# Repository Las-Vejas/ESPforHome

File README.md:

# ESPforHome

A super small ESP32C6 devboard perfect for ESPHome.

It uses the ESP32-C6-MINI-1 and ESPHome for the software. 14 GPIO pins along with 2 GND, 1 3V3 and 1 5V pins are available to the user. The board is exactly 30mm x 30mm.

## BOM

The bom is available in /BOM.csv

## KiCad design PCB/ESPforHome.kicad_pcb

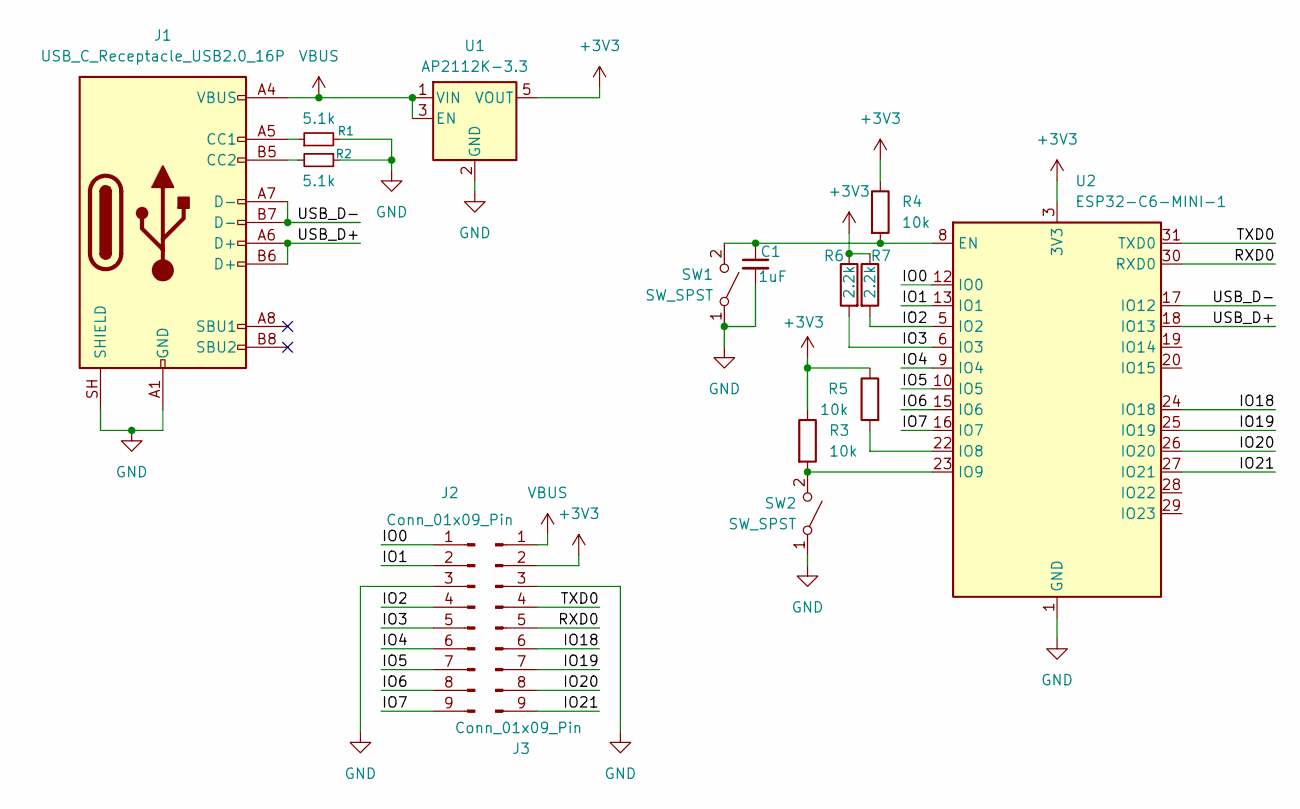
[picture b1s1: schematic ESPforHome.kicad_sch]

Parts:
C1: 1uF; C_0402_1005Metric; LCSC Part # C77009
J1: USB_C_Receptacle_USB2.0_16P; USB_C_Receptacle_GCT_USB4105-xx-A_16P_TopMnt_Horizontal; LCSC Part # C2765186
J2, J3: Conn_01x09_Pin; PinHeader_1x09_P2.54mm_Vertical; LCSC Part # C2883695
R1, R2: 5.1k; R_0402_1005Metric; LCSC Part # C2906874
R3, R4, R5: 10k; R_0402_1005Metric; LCSC Part # C2906861
R6, R7: 2.2k; R_0402_1005Metric; LCSC Part # C2906865
SW1, SW2: SW_SPST; SW_Push_SPST_NO_Alps_SKRK; LCSC Part # C49234124
U1: AP2112K-3.3; SOT-23-5; LCSC Part # C22365427
U2: ESP32-C6-MINI-1; LCSC Part # C5736265

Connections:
+3V3: J3.2, R3.1, R4.1, R5.1, R6.1, R7.1, U1.5 (VOUT), U2.3 (3V3)
/IO0: J2.1, U2.12 (IO0)
/IO1: J2.2, U2.13 (IO1)
/IO2: J2.4, R7.2, U2.5 (IO2)
/IO3: J2.5, R6.2, U2.6 (IO3)
/IO4: J2.6, U2.9 (IO4)
/IO5: J2.7, U2.10 (IO5)
/IO6: J2.8, U2.15 (IO6)
/IO7: J2.9, U2.16 (IO7)
/IO18: J3.6, U2.24 (IO18)
/IO19: J3.7, U2.25 (IO19)
/IO20: J3.8, U2.26 (IO20)
/IO21: J3.9, U2.27 (IO21)
/RXD0: J3.5, U2.30 (RXD0)
/TXD0: J3.4, U2.31 (TXD0)
/USB_D+: J1.A6 (D+), J1.B6 (D+), U2.18 (IO13)
/USB_D-: J1.A7 (D-), J1.B7 (D-), U2.17 (IO12)
GND: C1.2, J1.A1 (GND), J1.A12 (GND), J1.B1 (GND), J1.B12 (GND), J1.SH (SHIELD), J2.3, J3.3, R1.2, R2.1, SW1.1 (A), SW2.1 (A), U1.2 (GND), U2.1 (GND), U2.2 (GND), U2.11 (GND), U2.14 (GND), U2.36 (GND), U2.37 (GND), U2.38 (GND), U2.39 (GND), U2.40 (GND), U2.41 (GND), U2.42 (GND), U2.43 (GND), U2.44 (GND), U2.45 (GND), U2.46 (GND), U2.47 (GND), U2.48 (GND), U2.49 (GND), U2.50 (GND), U2.51 (GND), U2.52 (GND), U2.53 (GND)
unnamed: J1.A5 (CC1), R1.1
unnamed: J1.B5 (CC2), R2.2
unnamed: C1.1, R4.2, SW1.2 (B), U2.8 (EN)
unnamed: R3.2, SW2.2 (B), U2.23 (IO9)
unnamed: R5.2, U2.22 (IO8)
VBUS: J1.A4 (VBUS), J1.A9 (VBUS), J1.B4 (VBUS), J1.B9 (VBUS), J3.1, U1.1 (VIN), U1.3 (EN)

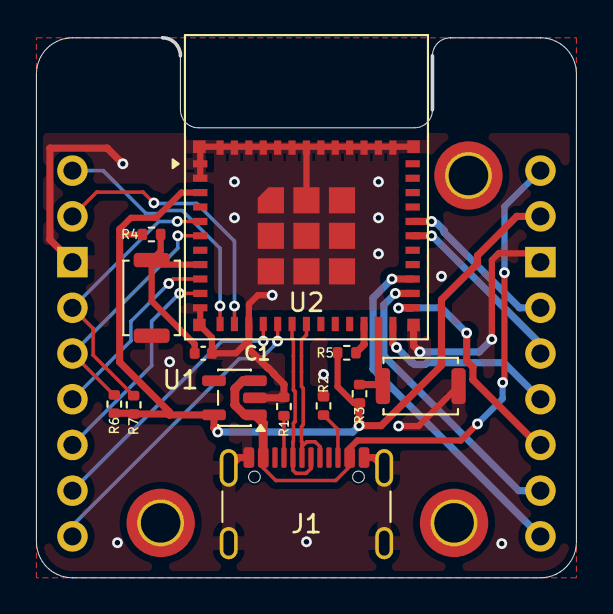
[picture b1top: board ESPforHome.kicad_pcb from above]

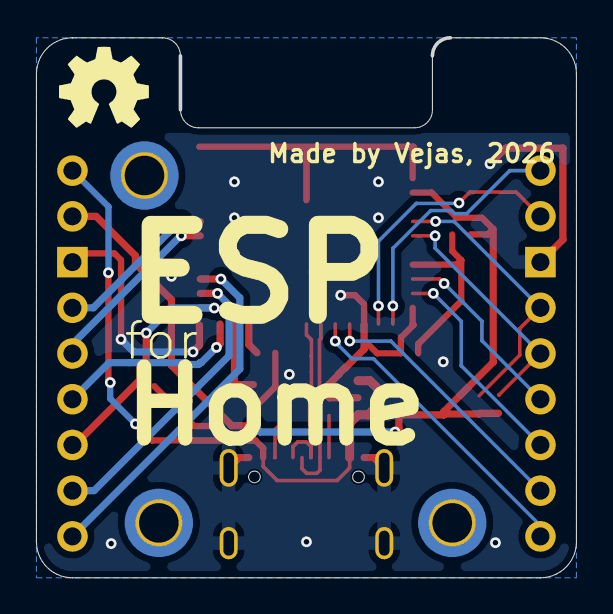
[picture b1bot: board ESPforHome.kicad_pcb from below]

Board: 2 copper layers, 30.0 x 30.0 mm, 15 parts (2 on the bottom side), 24 nets.

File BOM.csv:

Reference,Qty,LCSC Part #,Value,Price
C1,1,C77009,1uF,0.50 $US
"J2,J3",2,C2883695,Conn_01x09_Pin,1.93 $US
"R1,R2",2,C2906874,5.1k,0.15 $US
"R3,R4,R5",3,C2906861,10k,0.13 $US
"R6,R7",2,C2906865,2.2k,0.16 $US
"SW1,SW2",2,C49234124,SW_SPST,0.49 $US
U1,1,C22365427,AP2112K-3.3,0.38 $US
U2,1,C5736265,ESP32-C6-MINI-1,4.13 $US
J1,1,C2765186,USB_C_Receptacle_USB2.0_16P,1.44 $US
PCB,5,,,4.10 $US
Stencil,1,,,3.10 $US
TOTAL,,,,16.51 $US
